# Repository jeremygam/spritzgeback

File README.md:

# Spritzgeback
A suite of similar custom low profile mechanical keyboards running qmk

Note that this documentation is a work in progress. Will update with more and clean up later

### Basic Information

There are three variants of the spritzgeback keyboard: one with square spacing between keys, one with rectangular spacing between keys, and one with rectangular spacing that uses hotswap sockets.

Square:
Uses three laser-cut case layers plus a PCB layer. All layers are simply stacked so each is visible from the side. This keyboard should be best if using Kailh Choc v2 switches with more 'regular' profile keycaps like DSA, or if you generally prefer wider spacing between keys. Note that if you are using high profile keycaps, the keys may not depress all the way if you include the plate (case layer 3) - it should be fine to leave out layer 3 and just have the PCB as the top layer

Rect:
Uses four laser-cut case layers, with the PCB residing within one of the layers. This keyboard should be best if using Kailh Choc v1 switches with either the Kailh keycaps or MBK keycaps (which measure 16mm in height and 17mm in width).

Hotswap:
Similar to Rect but uses hotswap sockets instead of having switches soldered in place.

### Making a keyboard

If all you want to do is make one of these keyboards, just download the gerber files within the gerber_files directory and the eps files within the case_files directory. You can send the gerber files for production from a PCB manufacturing company. Note that the ".gml" file might need to be renamed to ".gm1" and the ".txt" file might need to be renamed to ".drl" depending on the company. The eps files can be directly sent for laser cutting. Double check that the dimensions are correct before submitting (315.6mm x 96mm for square, 308.9mm x 91.75mm for rect). Also note that the combined thickness of the PCB plus layer 2 should be at least 3mm (preferably a bit more for tolerance) to allow the switch pins adequate space within the case sandwich. For example, with a 1.6mm thick PCB, layer 2 should be at least 1.5mm or so thick. For keyboards where the PCB is totally enclosed in the case (i.e. rect and hotswap), layer 3 should be at least as thick as the PCB so that there isn't a gap between case layers.

Once all components except switches have been soldered, flash the keyboard with qmk (https://beta.docs.qmk.fm/tutorial/newbs_flashing), making sure to short the two "reset" holes while plugging in the PCB. After flashing, test the entire circuit by shorting out the switch holes and making sure the appropriate key is registered. Following that, switches or sockets can then be soldered in. The main step for case assembly is insertion of the threaded inserts into the case layers. If using acrylic, be careful not to crack the layers while inserting the threaded inserts - using the heat from a soldering iron to melt the plastic is highly recommended over using force. If using wood or bamboo layers, a hammer or mallet should be fine. The keyboard can then be screwed together, making sure not to overtighten the screws.

### BOM

Fill in later. See schematic for now

### Requirements

You will need to install and use qmk to flash your keyboard firmware https://qmk.fm/

You will need a footprint file for the USB-C connector Korean Hroparts Elec TYPE-C-31-M-17 from https://www.snapeda.com/parts/TYPE-C-31-M-12/HRO%20Electronics%20Co.,%20Ltd./view-part/

You may also want footprints for Kailh Choc v1 switches (PG1350) from https://github.com/daprice/keyswitches.pretty (also under CC BY-SA 4.0). I modified some of those original footprints to allow for either Choc v1 or v2 switches to be used (see SW_PG1353.kicad_mod and Kailh_socket_PG1353.kicad_mod in the JJG.pretty directory).

### Other Information

For info on how to design your own keyboard, check out Hadi's youtube channel (https://www.youtube.com/playlist?list=PLbtY7JsOJDYkHNuTmBtGgaWv_qipKeL-u) or Masterzen's tutorial (https://www.masterzen.fr/2020/05/03/designing-a-keyboard-part-1/)

Note that since each of the spritzgeback variants are highly similar electrically, they can all use the same qmk files

Note that if you make your own case files, ponoko recommends saving in eps file format with units set to mm instead of points.

------------------------

This work is licensed under a [Creative Commons Attribution-ShareAlike 4.0 International License](http://creativecommons.org/licenses/by-sa/4.0/).

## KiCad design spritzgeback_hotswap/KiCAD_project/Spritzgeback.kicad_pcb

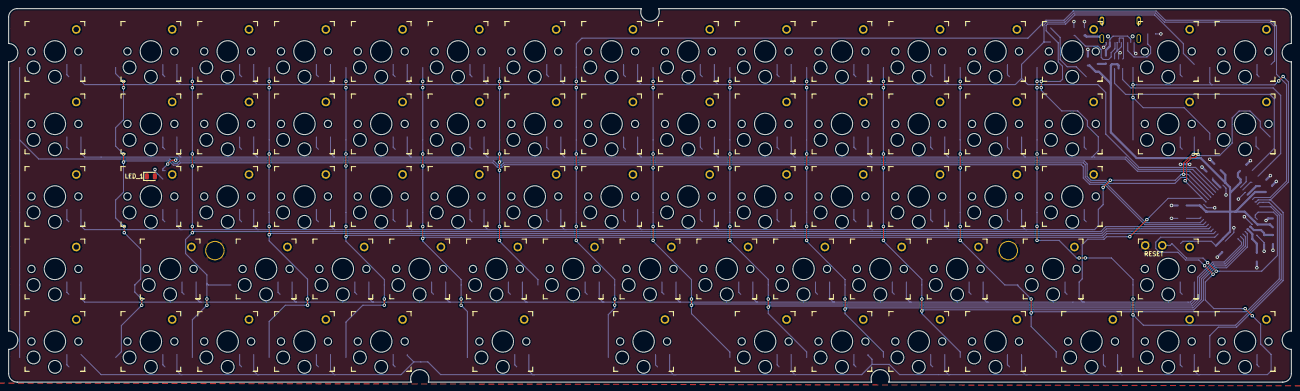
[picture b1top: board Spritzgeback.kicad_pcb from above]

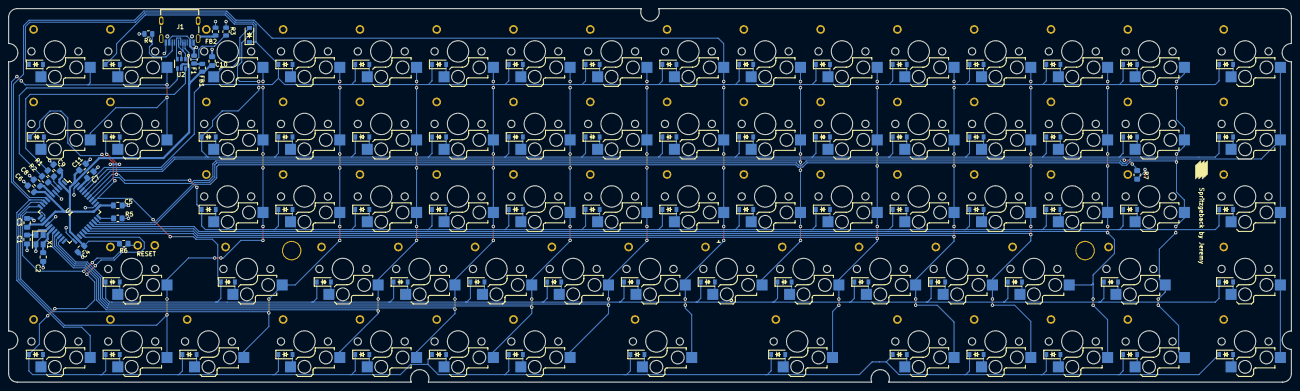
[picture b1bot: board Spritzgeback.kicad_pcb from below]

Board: 2 copper layers, 300.7 x 87.6 mm, 175 parts (99 on the bottom side), 115 nets.

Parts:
C1, C2: 22pF; C_0805_2012Metric_Pad1.18x1.45mm_HandSolder
C3, C4, C5, C6, C7, C11: 0.1u; C_0805_2012Metric_Pad1.18x1.45mm_HandSolder
C8, C10: 1u; C_0805_2012Metric_Pad1.18x1.45mm_HandSolder
C9: 4.7u; C_0805_2012Metric_Pad1.18x1.45mm_HandSolder
D_1, D_2, D_3, D_4, D_5, D_6, D_7, D_8, D_9, D_10, D_11, D_12, D_13, D_14, D_15, D_16, D_17, D_18, D_19, D_20, D_21, D_22, D_23, D_24, D_25, D_26, D_27, D_28, D_29, D_30, D_31, D_32, D_33, D_34, D_35, D_36, D_37, D_38, D_39, D_40, D_41, D_42, D_43, D_44, D_45, D_46, D_47, D_48, D_49, D_50, D_51, D_52, D_53, D_54, D_55, D_56, D_57, D_58, D_59, D_60, D_61, D_62, D_63, D_64, D_65, D_66, D_67, D_68, D_69, D_70, D_71, D_72, D_73, D_74: D_Small_ALT; D_SOD-123_silk
F1: Polyfuse_Small; R_0805_2012Metric
FB1, FB2: Ferrite_Bead_Small; R_0805_2012Metric
J1: USB_C_Receptacle; HRO_TYPE-C-31-M-12
LED_1: D_Small_ALT; LED_0805_2012Metric
R1, R2: 22; R_0805_2012Metric_Pad1.20x1.40mm_HandSolder
R3, R4: 5.1k; R_0805_2012Metric
R5, R6: 10k; R_0805_2012Metric_Pad1.20x1.40mm_HandSolder
R7: 330; R_0805_2012Metric_Pad1.20x1.40mm_HandSolder
RESET: RESET; reset_holes
S_1, S_2, S_3, S_4, S_5, S_6, S_7, S_8, S_9, S_10, S_11, S_12, S_13, S_14, S_15, S_16, S_17, S_18, S_19, S_20, S_21, S_22, S_23, S_24, S_25, S_26, S_27, S_28, S_29, S_30, S_31, S_32, S_33, S_34, S_35, S_36, S_37, S_38, S_39, S_40, S_41, S_42, S_43, S_44, S_45, S_46, S_47, S_48, S_49, S_50, S_51, S_52, S_53, S_54, S_55, S_56, S_57, S_58, S_59, S_60, S_61, S_62, S_63, S_64, S_65, S_66, S_67, S_68, S_69, S_70, S_71, S_72, S_73, S_74: SW_SPST; Kailh_socket_PG1353
U1: ATMEGA32U4; TQFP-44_10x10mm_P0.8mm
U2: USBLC6-2SC6; SOT-23-6
X1: 16MHz; Crystal_SMD_3225-4Pin_3.2x2.5mm

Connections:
AREF: C7.1, U1.42
Col_0: S_1.2, S_17.2, S_33.2, S_47.2, S_61.2, U1.32
Col_1: S_2.2, S_18.2, S_34.2, S_48.2, S_62.2, U1.31
Col_2: S_3.2, S_19.2, S_35.2, S_49.2, S_63.2, U1.30
Col_3: S_4.2, S_20.2, S_36.2, S_50.2, S_64.2, U1.29
Col_4: S_5.2, S_21.2, S_37.2, S_51.2, S_65.2, U1.28
Col_5: S_6.2, S_22.2, S_38.2, S_52.2, S_66.2, U1.27
Col_6: S_7.2, S_23.2, S_39.2, S_53.2, U1.37
Col_7: S_8.2, S_24.2, S_40.2, S_54.2, S_67.2, U1.8
Col_8: S_9.2, S_25.2, S_41.2, S_55.2, S_68.2, U1.21
Col_9: S_10.2, S_26.2, S_42.2, S_56.2, S_69.2, U1.20
Col_10: S_11.2, S_27.2, S_43.2, S_57.2, S_70.2, U1.19
Col_11: S_12.2, S_28.2, S_44.2, S_58.2, S_71.2, U1.18
Col_12: S_13.2, S_29.2, S_45.2, S_59.2, S_72.2, U1.11
Col_13: S_14.2, S_30.2, S_46.2, S_60.2, S_73.2, U1.10
Col_14: S_15.2, S_16.2, S_31.2, S_32.2, S_74.2, U1.9
D+: R2.2, U2.4
D-: R1.2, U2.6
Earth: C1.1, C2.1, C3.2, C4.2, C5.2, C6.2, C7.2, C8.2, C9.2, C10.2, C11.2, FB2.2, J1.A1, J1.A12, LED_1.1, R3.1, R4.1, R5.1, RESET.2, U1.5, U1.15, U1.23, U1.35, U1.43, U2.2, X1.2, X1.4
LED_1: R7.2, U1.39
unnamed: D_1.2, S_1.1
unnamed: D_2.2, S_2.1
unnamed: D_3.2, S_3.1
unnamed: D_4.2, S_4.1
unnamed: D_5.2, S_5.1
unnamed: D_6.2, S_6.1
unnamed: D_7.2, S_7.1
unnamed: D_8.2, S_8.1
unnamed: D_9.2, S_9.1
unnamed: D_10.2, S_10.1
unnamed: D_11.2, S_11.1
unnamed: D_12.2, S_12.1
unnamed: D_13.2, S_13.1
unnamed: D_14.2, S_14.1
unnamed: D_15.2, S_15.1
unnamed: D_16.2, S_16.1
unnamed: D_17.2, S_17.1
unnamed: D_18.2, S_18.1
unnamed: D_19.2, S_19.1
unnamed: D_20.2, S_20.1
unnamed: D_21.2, S_21.1
unnamed: D_22.2, S_22.1
unnamed: D_23.2, S_23.1
unnamed: D_24.2, S_24.1
unnamed: D_25.2, S_25.1
unnamed: D_26.2, S_26.1
unnamed: D_27.2, S_27.1
unnamed: D_28.2, S_28.1
unnamed: D_29.2, S_29.1
unnamed: D_30.2, S_30.1
unnamed: D_31.2, S_31.1
unnamed: D_32.2, S_32.1
unnamed: D_33.2, S_33.1
unnamed: D_34.2, S_34.1
unnamed: D_35.2, S_35.1
unnamed: D_36.2, S_36.1
unnamed: D_37.2, S_37.1
unnamed: D_38.2, S_38.1
unnamed: D_39.2, S_39.1
unnamed: D_40.2, S_40.1
unnamed: D_41.2, S_41.1
unnamed: D_42.2, S_42.1
unnamed: D_43.2, S_43.1
unnamed: D_44.2, S_44.1
unnamed: D_45.2, S_45.1
unnamed: D_46.2, S_46.1
unnamed: D_47.2, S_47.1
unnamed: D_48.2, S_48.1
unnamed: D_49.2, S_49.1
unnamed: D_50.2, S_50.1
unnamed: D_51.2, S_51.1
unnamed: D_52.2, S_52.1
unnamed: D_53.2, S_53.1
unnamed: D_54.2, S_54.1
unnamed: D_55.2, S_55.1
unnamed: D_56.2, S_56.1
unnamed: D_57.2, S_57.1
unnamed: D_58.2, S_58.1
unnamed: D_59.2, S_59.1
unnamed: D_60.2, S_60.1
unnamed: D_61.2, S_61.1
unnamed: D_62.2, S_62.1
unnamed: D_63.2, S_63.1
unnamed: D_64.2, S_64.1
unnamed: D_65.2, S_65.1
unnamed: D_66.2, S_66.1
unnamed: D_67.2, S_67.1
unnamed: D_68.2, S_68.1
unnamed: D_69.2, S_69.1
unnamed: D_70.2, S_70.1
unnamed: D_71.2, S_71.1
unnamed: D_72.2, S_72.1
unnamed: D_73.2, S_73.1
unnamed: D_74.2, S_74.1
unnamed: F1.1, FB1.2
unnamed: FB2.1, J1.S1
unnamed: J1.A5, R3.2
unnamed: J1.B5, R4.2
unnamed: LED_1.2, R7.1
unnamed: R1.1, U1.3
unnamed: R2.1, U1.4
unnamed: R5.2, U1.33
RESET: R6.1, RESET.1, U1.13
Row_0: D_1.1, D_2.1, D_3.1, D_4.1, D_5.1, D_6.1, D_7.1, D_8.1, D_9.1, D_10.1, D_11.1, D_12.1, D_13.1, D_14.1, D_16.1, U1.41
Row_1: D_15.1, D_17.1, D_18.1, D_19.1, D_20.1, D_21.1, D_22.1, D_23.1, D_24.1, D_25.1, D_26.1, D_27.1, D_28.1, D_29.1, D_30.1, U1.40
Row_2: D_31.1, D_33.1, D_34.1, D_35.1, D_36.1, D_37.1, D_38.1, D_39.1, D_40.1, D_41.1, D_42.1, D_43.1, D_44.1, D_45.1, D_46.1, U1.38
Row_3: D_32.1, D_47.1, D_48.1, D_49.1, D_50.1, D_51.1, D_52.1, D_53.1, D_54.1, D_55.1, D_56.1, D_57.1, D_58.1, D_59.1, D_60.1, U1.36
Row_4: D_61.1, D_62.1, D_63.1, D_64.1, D_65.1, D_66.1, D_67.1, D_68.1, D_69.1, D_70.1, D_71.1, D_72.1, D_73.1, D_74.1, U1.26
UCAP: C8.1, U1.6
USB_D+: J1.A6, J1.B6, U2.3
USB_D-: J1.A7, J1.B7, U2.1
VBUS: F1.2, J1.A4, J1.A9
VCC: C3.1, C4.1, C5.1, C6.1, C9.1, C10.1, C11.1, FB1.1, R6.2, U1.2, U1.7, U1.14, U1.24, U1.34, U1.44, U2.5
XTAL1: C1.2, U1.16, X1.1
XTAL2: C2.2, U1.17, X1.3

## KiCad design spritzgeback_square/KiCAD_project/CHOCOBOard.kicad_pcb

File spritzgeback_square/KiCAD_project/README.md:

note that I wanted to rename the project from CHOCOBOard to spritzgeback, but KiCAD doesn't handle renaming easily so I've kept the original name here

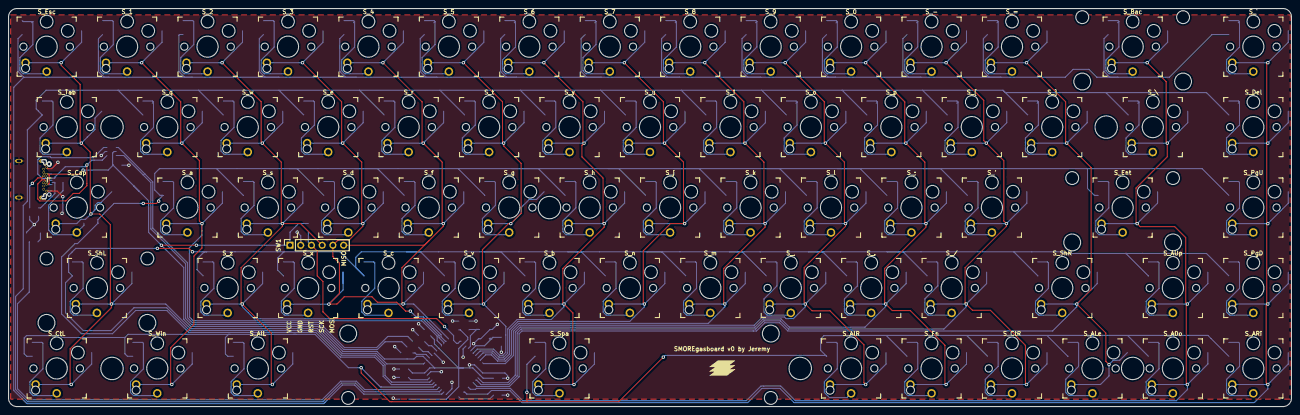
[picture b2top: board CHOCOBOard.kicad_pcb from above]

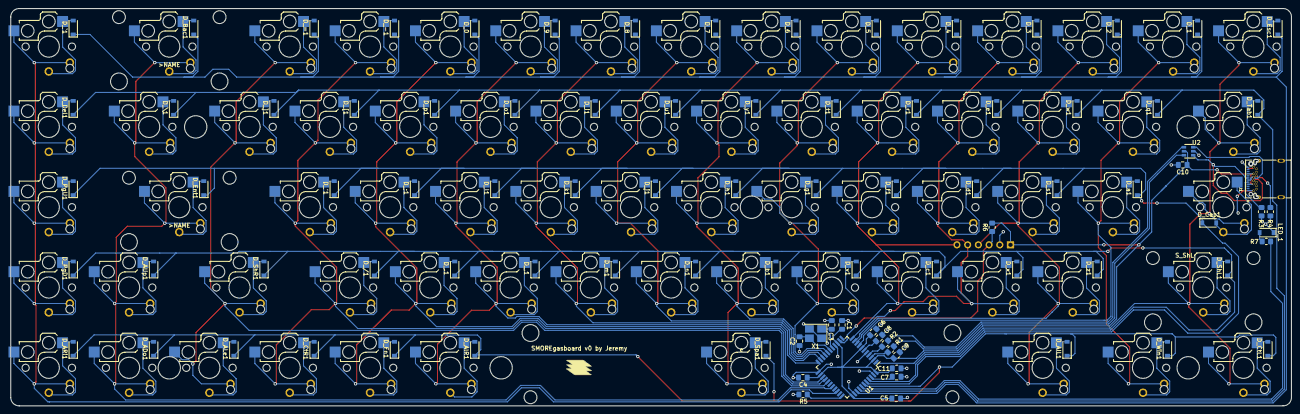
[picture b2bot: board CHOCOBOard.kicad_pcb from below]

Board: 2 copper layers, 303.8 x 94.2 mm, 163 parts (91 on the bottom side), 106 nets.

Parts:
>NAME: >VALUE; stabilizer_holes_200
>NAME#2: >VALUE; stabilizer_holes_225
C1, C2: 22pF; C_0805_2012Metric_Pad1.18x1.45mm_HandSolder
C3, C4, C5, C6, C7, C11: 0.1u; C_0805_2012Metric_Pad1.18x1.45mm_HandSolder
C8, C10: 1u; C_0805_2012Metric_Pad1.18x1.45mm_HandSolder
C9: 4.7u; C_0805_2012Metric_Pad1.18x1.45mm_HandSolder
D_0, D_1, D_2, D_3, D_4, D_5, D_6, D_7, D_8, D_9, D_.1: D_Small_ALT; D_SOD-123
D_'1: D_Small_ALT; D_SOD-123
D_,1: D_Small_ALT; D_SOD-123
D_-1: D_Small_ALT; D_SOD-123
D_/1: D_Small_ALT; D_SOD-123
D_;1: D_Small_ALT; D_SOD-123
D_=1: D_Small_ALT; D_SOD-123
D_ADo1: D_Small_ALT; D_SOD-123
D_ALe1: D_Small_ALT; D_SOD-123
D_ARi1: D_Small_ALT; D_SOD-123
D_AUp1: D_Small_ALT; D_SOD-123
D_AlL1: D_Small_ALT; D_SOD-123
D_AlR1: D_Small_ALT; D_SOD-123
D_Bac1: D_Small_ALT; D_SOD-123
D_Cap1: D_Small_ALT; D_SOD-123
D_CtL1: D_Small_ALT; D_SOD-123
D_CtR1: D_Small_ALT; D_SOD-123
D_Del1: D_Small_ALT; D_SOD-123
D_Ent1: D_Small_ALT; D_SOD-123
D_Esc1: D_Small_ALT; D_SOD-123
D_Fn1: D_Small_ALT; D_SOD-123
D_PgD1: D_Small_ALT; D_SOD-123
D_PgU1: D_Small_ALT; D_SOD-123
D_ShL1: D_Small_ALT; D_SOD-123
D_ShR1: D_Small_ALT; D_SOD-123
D_Spa1: D_Small_ALT; D_SOD-123
D_Tab1: D_Small_ALT; D_SOD-123
D_Win1: D_Small_ALT; D_SOD-123
D_[1: D_Small_ALT; D_SOD-123
D_\1: D_Small_ALT; D_SOD-123
D_]1: D_Small_ALT; D_SOD-123
D_`1: D_Small_ALT; D_SOD-123
D_a1: D_Small_ALT; D_SOD-123
D_b1: D_Small_ALT; D_SOD-123
D_c1: D_Small_ALT; D_SOD-123
D_d1: D_Small_ALT; D_SOD-123
D_e1: D_Small_ALT; D_SOD-123
D_f1: D_Small_ALT; D_SOD-123
D_g1: D_Small_ALT; D_SOD-123
D_h1: D_Small_ALT; D_SOD-123
D_i1: D_Small_ALT; D_SOD-123
D_j1: D_Small_ALT; D_SOD-123
D_k1: D_Small_ALT; D_SOD-123
D_l1: D_Small_ALT; D_SOD-123
D_m1: D_Small_ALT; D_SOD-123
D_n1: D_Small_ALT; D_SOD-123
D_o1: D_Small_ALT; D_SOD-123
D_p1: D_Small_ALT; D_SOD-123
D_q1: D_Small_ALT; D_SOD-123
D_r1: D_Small_ALT; D_SOD-123
D_s1: D_Small_ALT; D_SOD-123
D_t1: D_Small_ALT; D_SOD-123
D_u1: D_Small_ALT; D_SOD-123
D_v1: D_Small_ALT; D_SOD-123
D_w1: D_Small_ALT; D_SOD-123
D_x1: D_Small_ALT; D_SOD-123
D_y1: D_Small_ALT; D_SOD-123
D_z1: D_Small_ALT; D_SOD-123
J1: USB_C_Receptacle; CUI_UJ31-CH-31-SMT-TR
LED_1: D_Small_ALT; D_SOD-123
R1, R2: 22; R_0805_2012Metric_Pad1.20x1.40mm_HandSolder
R3, R4: 5.1k; R_0805_2012Metric_Pad1.20x1.40mm_HandSolder
R5, R6: 10k; R_0805_2012Metric_Pad1.20x1.40mm_HandSolder
R7: 330; R_0805_2012Metric_Pad1.20x1.40mm_HandSolder
SW1: RESET; PinSocket_1x06_P2.54mm_Vertical
S_0, S_1, S_2, S_3, S_4, S_5, S_6, S_7, S_8, S_9, S_.: SW_SPST; Kailh_socket_PG1353_solder_PG1350
S_': SW_SPST; Kailh_socket_PG1353_solder_PG1350
S_,: SW_SPST; Kailh_socket_PG1353_solder_PG1350
S_-: SW_SPST; Kailh_socket_PG1353_solder_PG1350
S_/: SW_SPST; Kailh_socket_PG1353_solder_PG1350
S_;: SW_SPST; Kailh_socket_PG1353_solder_PG1350
S_=: SW_SPST; Kailh_socket_PG1353_solder_PG1350
S_ADo: SW_SPST; Kailh_socket_PG1353_solder_PG1350
S_ALe: SW_SPST; Kailh_socket_PG1353_solder_PG1350
S_ARi: SW_SPST; Kailh_socket_PG1353_solder_PG1350
S_AUp: SW_SPST; Kailh_socket_PG1353_solder_PG1350
S_AlL: SW_SPST; Kailh_socket_PG1353_solder_PG1350
S_AlR: SW_SPST; Kailh_socket_PG1353_solder_PG1350
S_Bac: SW_SPST; Kailh_socket_PG1353_solder_PG1350
S_Cap: SW_SPST; Kailh_socket_PG1353_solder_PG1350
S_CtL: SW_SPST; Kailh_socket_PG1353_solder_PG1350
S_CtR: SW_SPST; Kailh_socket_PG1353_solder_PG1350
S_Del: SW_SPST; Kailh_socket_PG1353_solder_PG1350
S_Ent: SW_SPST; Kailh_socket_PG1353_solder_PG1350
S_Esc: SW_SPST; Kailh_socket_PG1353_solder_PG1350
S_Fn: SW_SPST; Kailh_socket_PG1353_solder_PG1350
S_PgD: SW_SPST; Kailh_socket_PG1353_solder_PG1350
S_PgU: SW_SPST; Kailh_socket_PG1353_solder_PG1350
S_ShL: SW_SPST; Kailh_socket_PG1353_solder_PG1350
S_ShR: SW_SPST; Kailh_socket_PG1353_solder_PG1350
S_Spa: SW_SPST; Kailh_socket_PG1353_solder_PG1350
S_Tab: SW_SPST; Kailh_socket_PG1353_solder_PG1350
S_Win: SW_SPST; Kailh_socket_PG1353_solder_PG1350
S_[: SW_SPST; Kailh_socket_PG1353_solder_PG1350
S_\: SW_SPST; Kailh_socket_PG1353_solder_PG1350
S_]: SW_SPST; Kailh_socket_PG1353_solder_PG1350
S_`: SW_SPST; Kailh_socket_PG1353_solder_PG1350
S_a: SW_SPST; Kailh_socket_PG1353_solder_PG1350
S_b: SW_SPST; Kailh_socket_PG1353_solder_PG1350
S_c: SW_SPST; Kailh_socket_PG1353_solder_PG1350
S_d: SW_SPST; Kailh_socket_PG1353_solder_PG1350
S_e: SW_SPST; Kailh_socket_PG1353_solder_PG1350
S_f: SW_SPST; Kailh_socket_PG1353_solder_PG1350
S_g: SW_SPST; Kailh_socket_PG1353_solder_PG1350
S_h: SW_SPST; Kailh_socket_PG1353_solder_PG1350
S_i: SW_SPST; Kailh_socket_PG1353_solder_PG1350
S_j: SW_SPST; Kailh_socket_PG1353_solder_PG1350
S_k: SW_SPST; Kailh_socket_PG1353_solder_PG1350
S_l: SW_SPST; Kailh_socket_PG1353_solder_PG1350
S_m: SW_SPST; Kailh_socket_PG1353_solder_PG1350
S_n: SW_SPST; Kailh_socket_PG1353_solder_PG1350
S_o: SW_SPST; Kailh_socket_PG1353_solder_PG1350
S_p: SW_SPST; Kailh_socket_PG1353_solder_PG1350
S_q: SW_SPST; Kailh_socket_PG1353_solder_PG1350
S_r: SW_SPST; Kailh_socket_PG1353_solder_PG1350
S_s: SW_SPST; Kailh_socket_PG1353_solder_PG1350
S_t: SW_SPST; Kailh_socket_PG1353_solder_PG1350
S_u: SW_SPST; Kailh_socket_PG1353_solder_PG1350
S_v: SW_SPST; Kailh_socket_PG1353_solder_PG1350
S_w: SW_SPST; Kailh_socket_PG1353_solder_PG1350
S_x: SW_SPST; Kailh_socket_PG1353_solder_PG1350
S_y: SW_SPST; Kailh_socket_PG1353_solder_PG1350
S_z: SW_SPST; Kailh_socket_PG1353_solder_PG1350
U1: ATMEGA32U4; TQFP-44_10x10mm_P0.8mm
U2: USBLC6-2SC6; SOT-23-6
X1: 16MHz; Crystal_SMD_SeikoEpson_FA238-4Pin_3.2x2.5mm_HandSoldering
e: >VALUE; stabilizer_holes_625

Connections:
AREF: C7.1, U1.42
Col_0: S_Cap.2, S_CtL.2, S_Esc.2, S_ShL.2, S_Tab.2, U1.1
Col_1: S_1.2, S_Win.2, S_a.2, S_q.2, U1.8
Col_2: SW1.4, S_2.2, S_AlL.2, S_s.2, S_w.2, S_z.2, U1.9
Col_3: SW1.5, S_3.2, S_d.2, S_e.2, S_x.2, U1.10
Col_4: SW1.6, S_4.2, S_c.2, S_f.2, S_r.2, U1.11
Col_5: S_5.2, S_g.2, S_t.2, S_v.2, U1.18
Col_6: S_6.2, S_Spa.2, S_b.2, S_h.2, S_y.2, U1.19
Col_7: S_7.2, S_j.2, S_n.2, S_u.2, U1.20
Col_8: S_8.2, S_i.2, S_k.2, S_m.2, U1.21
Col_9: S_9.2, S_,.2, S_AlR.2, S_l.2, S_o.2, U1.22
Col_10: S_0.2, S_..2, S_;.2, S_Fn.2, S_p.2, U1.25
Col_11: S_'.2, S_-.2, S_/.2, S_CtR.2, S_[.2, U1.26
Col_12: S_=.2, S_ALe.2, S_ShR.2, S_].2, U1.27
Col_13: S_ADo.2, S_AUp.2, S_Bac.2, S_Ent.2, S_\.2, U1.29
Col_14: S_ARi.2, S_Del.2, S_PgD.2, S_PgU.2, S_`.2, U1.31
D+: R2.2, U2.4
D-: R1.2, U2.6
Earth: C1.1, C2.1, C3.2, C4.2, C5.2, C6.2, C7.2, C8.2, C9.2, C10.2, C11.2, J1.A1, J1.A12, J1.B1, J1.B12, J1.S1, J1.S2, J1.S3, J1.S4, J1.S5, J1.S6, LED_1.1, R3.1, R4.1, R5.1, SW1.2, U1.5, U1.15, U1.23, U1.35, U1.43, U2.2, X1.2, X1.4
LED_1: R7.2, U1.38
unnamed: D_0.2, S_0.1
unnamed: D_1.2, S_1.1
unnamed: D_2.2, S_2.1
unnamed: D_3.2, S_3.1
unnamed: D_4.2, S_4.1
unnamed: D_5.2, S_5.1
unnamed: D_6.2, S_6.1
unnamed: D_7.2, S_7.1
unnamed: D_8.2, S_8.1
unnamed: D_9.2, S_9.1
unnamed: D_'1.2, S_'.1
unnamed: D_,1.2, S_,.1
unnamed: D_-1.2, S_-.1
unnamed: D_.1.2, S_..1
unnamed: D_/1.2, S_/.1
unnamed: D_;1.2, S_;.1
unnamed: D_=1.2, S_=.1
unnamed: D_ADo1.2, S_ADo.1
unnamed: D_ALe1.2, S_ALe.1
unnamed: D_ARi1.2, S_ARi.1
unnamed: D_AUp1.2, S_AUp.1
unnamed: D_AlL1.2, S_AlL.1
unnamed: D_AlR1.2, S_AlR.1
unnamed: D_Bac1.2, S_Bac.1
unnamed: D_Cap1.2, S_Cap.1
unnamed: D_CtL1.2, S_CtL.1
unnamed: D_CtR1.2, S_CtR.1
unnamed: D_Del1.2, S_Del.1
unnamed: D_Ent1.2, S_Ent.1
unnamed: D_Esc1.2, S_Esc.1
unnamed: D_Fn1.2, S_Fn.1
unnamed: D_PgD1.2, S_PgD.1
unnamed: D_PgU1.2, S_PgU.1
unnamed: D_ShL1.2, S_ShL.1
unnamed: D_ShR1.2, S_ShR.1
unnamed: D_Spa1.2, S_Spa.1
unnamed: D_Tab1.2, S_Tab.1
unnamed: D_Win1.2, S_Win.1
unnamed: D_[1.2, S_[.1
unnamed: D_\1.2, S_\.1
unnamed: D_]1.2, S_].1
unnamed: D_`1.2, S_`.1
unnamed: D_a1.2, S_a.1
unnamed: D_b1.2, S_b.1
unnamed: D_c1.2, S_c.1
unnamed: D_d1.2, S_d.1
unnamed: D_e1.2, S_e.1
unnamed: D_f1.2, S_f.1
unnamed: D_g1.2, S_g.1
unnamed: D_h1.2, S_h.1
unnamed: D_i1.2, S_i.1
unnamed: D_j1.2, S_j.1
unnamed: D_k1.2, S_k.1
unnamed: D_l1.2, S_l.1
unnamed: D_m1.2, S_m.1
unnamed: D_n1.2, S_n.1
unnamed: D_o1.2, S_o.1
unnamed: D_p1.2, S_p.1
unnamed: D_q1.2, S_q.1
unnamed: D_r1.2, S_r.1
unnamed: D_s1.2, S_s.1
unnamed: D_t1.2, S_t.1
unnamed: D_u1.2, S_u.1
unnamed: D_v1.2, S_v.1
unnamed: D_w1.2, S_w.1
unnamed: D_x1.2, S_x.1
unnamed: D_y1.2, S_y.1
unnamed: D_z1.2, S_z.1
unnamed: J1.A5, R3.2
unnamed: J1.B5, R4.2
unnamed: LED_1.2, R7.1
unnamed: R1.1, U1.3
unnamed: R2.1, U1.4
unnamed: R5.2, U1.33
RESET: R6.1, SW1.3, U1.13
Row_0: D_0.1, D_1.1, D_2.1, D_3.1, D_4.1, D_5.1, D_6.1, D_7.1, D_8.1, D_9.1, D_-1.1, D_=1.1, D_Bac1.1, D_Esc1.1, D_`1.1, U1.36
Row_1: D_Del1.1, D_Tab1.1, D_[1.1, D_\1.1, D_]1.1, D_e1.1, D_i1.1, D_o1.1, D_p1.1, D_q1.1, D_r1.1, D_t1.1, D_u1.1, D_w1.1, D_y1.1, U1.37
Row_2: D_'1.1, D_;1.1, D_Cap1.1, D_Ent1.1, D_PgU1.1, D_a1.1, D_d1.1, D_f1.1, D_g1.1, D_h1.1, D_j1.1, D_k1.1, D_l1.1, D_s1.1, U1.40
Row_3: D_,1.1, D_.1.1, D_/1.1, D_AUp1.1, D_PgD1.1, D_ShL1.1, D_ShR1.1, D_b1.1, D_c1.1, D_m1.1, D_n1.1, D_v1.1, D_x1.1, D_z1.1, U1.41
Row_4: D_ADo1.1, D_ALe1.1, D_ARi1.1, D_AlL1.1, D_AlR1.1, D_CtL1.1, D_CtR1.1, D_Fn1.1, D_Spa1.1, D_Win1.1, U1.39
UCAP: C8.1, U1.6
USB_D+: J1.A6, J1.B6, U2.3
USB_D-: J1.A7, J1.B7, U2.1
VBUS: C3.1, C4.1, C5.1, C6.1, C9.1, C10.1, C11.1, J1.A4, J1.A9, J1.B4, J1.B9, R6.2, SW1.1, U1.2, U1.7, U1.14, U1.24, U1.34, U1.44, U2.5
XTAL1: C1.2, U1.16, X1.1
XTAL2: C2.2, U1.17, X1.3

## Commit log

2021-04-11 gitignore
2021-04-11 clean up
2021-04-11 license
2021-04-11 Create LICENSE
2021-04-11 kicad footprints
2021-04-11 update code for case
2021-04-11 Update LICENSE
2021-04-11 rename files
2021-05-03 add hotswap eps
2021-05-24 numpad keymap added
2021-06-03 updated rect case files
2021-06-03 case files
2021-08-07 add_hotswap
